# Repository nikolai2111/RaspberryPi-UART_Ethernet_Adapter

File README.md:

<!-- Improved compatibility of back to top link: See: https://github.com/othneildrew/Best-README-Template/pull/73 -->

<!--
*** Thanks for checking out the Best-README-Template. If you have a suggestion
*** that would make this better, please fork the repo and create a pull request
*** or simply open an issue with the tag "enhancement".
*** Don't forget to give the project a star!
*** Thanks again! Now go create something AMAZING! :D
-->

<!-- PROJECT SHIELDS -->
<!--
*** I'm using markdown "reference style" links for readability.
*** Reference links are enclosed in brackets [ ] instead of parentheses ( ).
*** See the bottom of this document for the declaration of the reference variables
*** for contributors-url, forks-url, etc. This is an optional, concise syntax you may use.
*** https://www.markdownguide.org/basic-syntax/#reference-style-links
-->
[![Contributors][contributors-shield]][contributors-url]
[![Forks][forks-shield]][forks-url]
[![Stargazers][stars-shield]][stars-url]
[![Issues][issues-shield]][issues-url]
[![MIT License][license-shield]][license-url]

<!-- PROJECT LOGO -->
<br />
<div align="center">

<h3 align="center">Raspberry Pi UART to Ethernet Adapter</h3>

  <p align="center">
    This adapter board enables the creation of a stand-alone, network-compatible device using any Raspberry Pi compatible UART daughterboard.
    <br />
    <a href="https://github.com/nikolai2111/RaspberryPi-UART_Ethernet_Adapter"><strong>Explore the docs »</strong></a>
    <br />
    <br />
    <a href="https://github.com/nikolai2111/RaspberryPi-UART_Ethernet_Adapter">View Demo</a>
    ·
    <a href="https://github.com/nikolai2111/RaspberryPi-UART_Ethernet_Adapter/issues/new?labels=bug&template=bug-report---.md">Report Bug</a>
    ·
    <a href="https://github.com/nikolai2111/RaspberryPi-UART_Ethernet_Adapter/issues/new?labels=enhancement&template=feature-request---.md">Request Feature</a>
  </p>
</div>

<!-- TABLE OF CONTENTS -->
<details>
  <summary>Table of Contents</summary>
  <ol>
    <li>
      <a href="#about-the-project">About The Project</a>
      <ul>
        <li><a href="#built-with">Built With</a></li>
      </ul>
    </li>
    <li>
      <a href="#getting-started">Getting Started</a>
      <ul>
        <li><a href="#prerequisites">Prerequisites</a></li>
        <li><a href="#Configure WIZ750SR">Configure WIZ750SR</a></li>
        <li><a href="#Confgure Z-Wave JS UI">Confgure Z-Wave JS UI</a></li>
      </ul>
    </li>
    <li><a href="#usage">Usage</a></li>
    <li><a href="#roadmap">Roadmap</a></li>
    <li><a href="#contributing">Contributing</a></li>
    <li><a href="#license">License</a></li>
    <li><a href="#contact">Contact</a></li>
    <li><a href="#acknowledgments">Acknowledgments</a></li>
  </ol>
</details>

<!-- ABOUT THE PROJECT -->
## About The Project

This adapter board enables the creation of a stand-alone, network-compatible device using any Raspberry Pi compatible UART daughterboard. The adapter board is used to connect the daughterboard of the Raspberry Pi and [WIZ750SR](https://docs.wiznet.io/Product/S2E-Module/WIZ750SR)-TTL. The adapter board connects the daughterboard of the Raspberry Pi to the [WIZ750SR](https://docs.wiznet.io/Product/S2E-Module/WIZ750SR)-TTL. It also provides a 5V and 3.3V power supply where necessary.

The adapter board was initially designed to connect the [RaZberry 7 Pro](https://z-wave.me/products/razberry/#slide-1) to [Home Assistant](https://www.home-assistant.io/) via TCP, without using a Raspberry Pi as a server. It can also be used with any Raspberry Pi daughterboard that only needs the TTL-UART interface. However, the following README refers to the use of the [RaZberry 7 Pro](https://z-wave.me/products/razberry/#slide-1) with [Home Assistant](https://www.home-assistant.io/). It is possible to map three GPIOs to the header, although this has not been tested yet.

The board or as a kit (incl. [WIZ750SR](https://www.digikey.de/de/products/detail/wiznet/WIZ750SR-TTL/8789618)) can be purchased [here](https://www.tindie.com/products/nikolai2111/raspberry-pi-uart-to-ethernet-adapter/). The board is available with three power supply options (power supply not inlcuded):
* [Barrel Jack 2.1x5.5 mm](https://www.digikey.com/en/products/detail/cui-devices/PJ-037A/1644545)
* [USB Micro](https://www.digikey.de/de/products/detail/amphenol-cs-fci/10118194-0001LF/2785389)
* [USB C](https://www.digikey.ch/de/products/detail/gct/USB4125-GF-A/13547388)

<p align="right">(<a href="#readme-top">back to top</a>)</p>

### Built With

* [][Kicad-url]

<p align="right">(<a href="#readme-top">back to top</a>)</p>

<!-- GETTING STARTED -->
## Getting Started

### Prerequisites
* [Home Assistant](https://www.home-assistant.io/) is running
* [Z-Wave JS UI](https://www.home-assistant.io/integrations/zwave_js/) installed
* [WIZnet-S2E-Tool-GUI](https://github.com/Wiznet/WIZnet-S2E-Tool-GUI) downloaded

### Configure WIZ750SR
1. Open the [WIZnet-S2E-Tool-GUI](https://github.com/Wiznet/WIZnet-S2E-Tool-GUI)
2. Click `Device Search`
3. Select device with double click
4. Set the `Basic Settings` as shown in the picture below

### Confgure Z-Wave JS UI
1. Open [Home Assistant](homeassistant.local)
2. Open `Add-ons`
3. Click on `Z-Wave JS UI`
4. Start the add-on, if it's not running yet
5. Click on `OPEN WEB UI`
6. Go to `Settings`
7. Go to `Z-Wave`
8. And enter the IP and port below the `Serial Port` as shown in the picture blow. Use the scheme `tcp://your-ip:port`

<!-- USAGE EXAMPLES -->
## Usage

Use this space to show useful examples of how a project can be used. Additional screenshots, code examples and demos work well in this space. You may also link to more resources.

_For more examples, please refer to the [Documentation](https://example.com)_

<p align="right">(<a href="#readme-top">back to top</a>)</p>

<!-- ROADMAP -->
## Roadmap

* [ ] Test more than one device
* [ ] Offer [WIZ750SR](https://docs.wiznet.io/Product/S2E-Module/WIZ750SR) in the shop
* [ ] Offer PoE adapter in the shop

See the [open issues](https://github.com/nikolai2111/RaspberryPi-UART_Ethernet_Adapter/issues) for a full list of proposed features (and known issues).

<p align="right">(<a href="#readme-top">back to top</a>)</p>

<!-- CONTRIBUTING -->
## Contributing

Contributions are what make the open source community such an amazing place to learn, inspire, and create. Any contributions you make are **greatly appreciated**.

If you have a suggestion that would make this better, please fork the repo and create a pull request. You can also simply open an issue with the tag "enhancement".
Don't forget to give the project a star! Thanks again!

1. Fork the Project
2. Create your Feature Branch (`git checkout -b feature/AmazingFeature`)
3. Commit your Changes (`git commit -m 'Add some AmazingFeature'`)
4. Push to the Branch (`git push origin feature/AmazingFeature`)
5. Open a Pull Request

<p align="right">(<a href="#readme-top">back to top</a>)</p>

<!-- LICENSE -->
## License

Distributed under the [CERN-OHL-P](LICENSE) License. See `LICENSE` for more information. The license for all other sources remains the same and is still valid.

<p align="right">(<a href="#readme-top">back to top</a>)</p>

<!-- CONTACT -->
## Contact

Nikolai Zoller - [nikolai.zoller@hotmail.com](mailto:nikolai.zoller@hotmail.com)

Project Link: [https://github.com/nikolai2111/RaspberryPi-UART_Ethernet_Adapter](https://github.com/nikolai2111/RaspberryPi-UART_Ethernet_Adapter)

<p align="right">(<a href="#readme-top">back to top</a>)</p>

<!-- ACKNOWLEDGMENTS -->
## Acknowledgments

The main concept was initially proposed by an anonymous colleague. The development, production, and sale are carried out with their consent.

<p align="right">(<a href="#readme-top">back to top</a>)</p>

Source: [Best-README-Template](https://github.com/othneildrew/Best-README-Template)

<!-- MARKDOWN LINKS & IMAGES -->
<!-- https://www.markdownguide.org/basic-syntax/#reference-style-links -->
[contributors-shield]: https://img.shields.io/github/contributors/nikolai2111/RaspberryPi-UART_Ethernet_Adapter.svg?style=for-the-badge
[contributors-url]: https://github.com/nikolai2111/RaspberryPi-UART_Ethernet_Adapter/graphs/contributors
[forks-shield]: https://img.shields.io/github/forks/nikolai2111/RaspberryPi-UART_Ethernet_Adapter.svg?style=for-the-badge
[forks-url]: https://github.com/nikolai2111/RaspberryPi-UART_Ethernet_Adapter/network/members
[stars-shield]: https://img.shields.io/github/stars/nikolai2111/RaspberryPi-UART_Ethernet_Adapter.svg?style=for-the-badge
[stars-url]: https://github.com/nikolai2111/RaspberryPi-UART_Ethernet_Adapter/stargazers
[issues-shield]: https://img.shields.io/github/issues/nikolai2111/RaspberryPi-UART_Ethernet_Adapter.svg?style=for-the-badge
[issues-url]: https://github.com/nikolai2111/RaspberryPi-UART_Ethernet_Adapter/issues
[license-shield]: https://img.shields.io/github/license/nikolai2111/RaspberryPi-UART_Ethernet_Adapter.svg?style=for-the-badge
[license-url]: https://github.com/nikolai2111/RaspberryPi-UART_Ethernet_Adapter/blob/master/LICENSE.txt
[Kicad-logo]: https://upload.wikimedia.org/wikipedia/commons/5/59/KiCad-Logo.svg
[Kicad-url]: https://www.kicad.org/

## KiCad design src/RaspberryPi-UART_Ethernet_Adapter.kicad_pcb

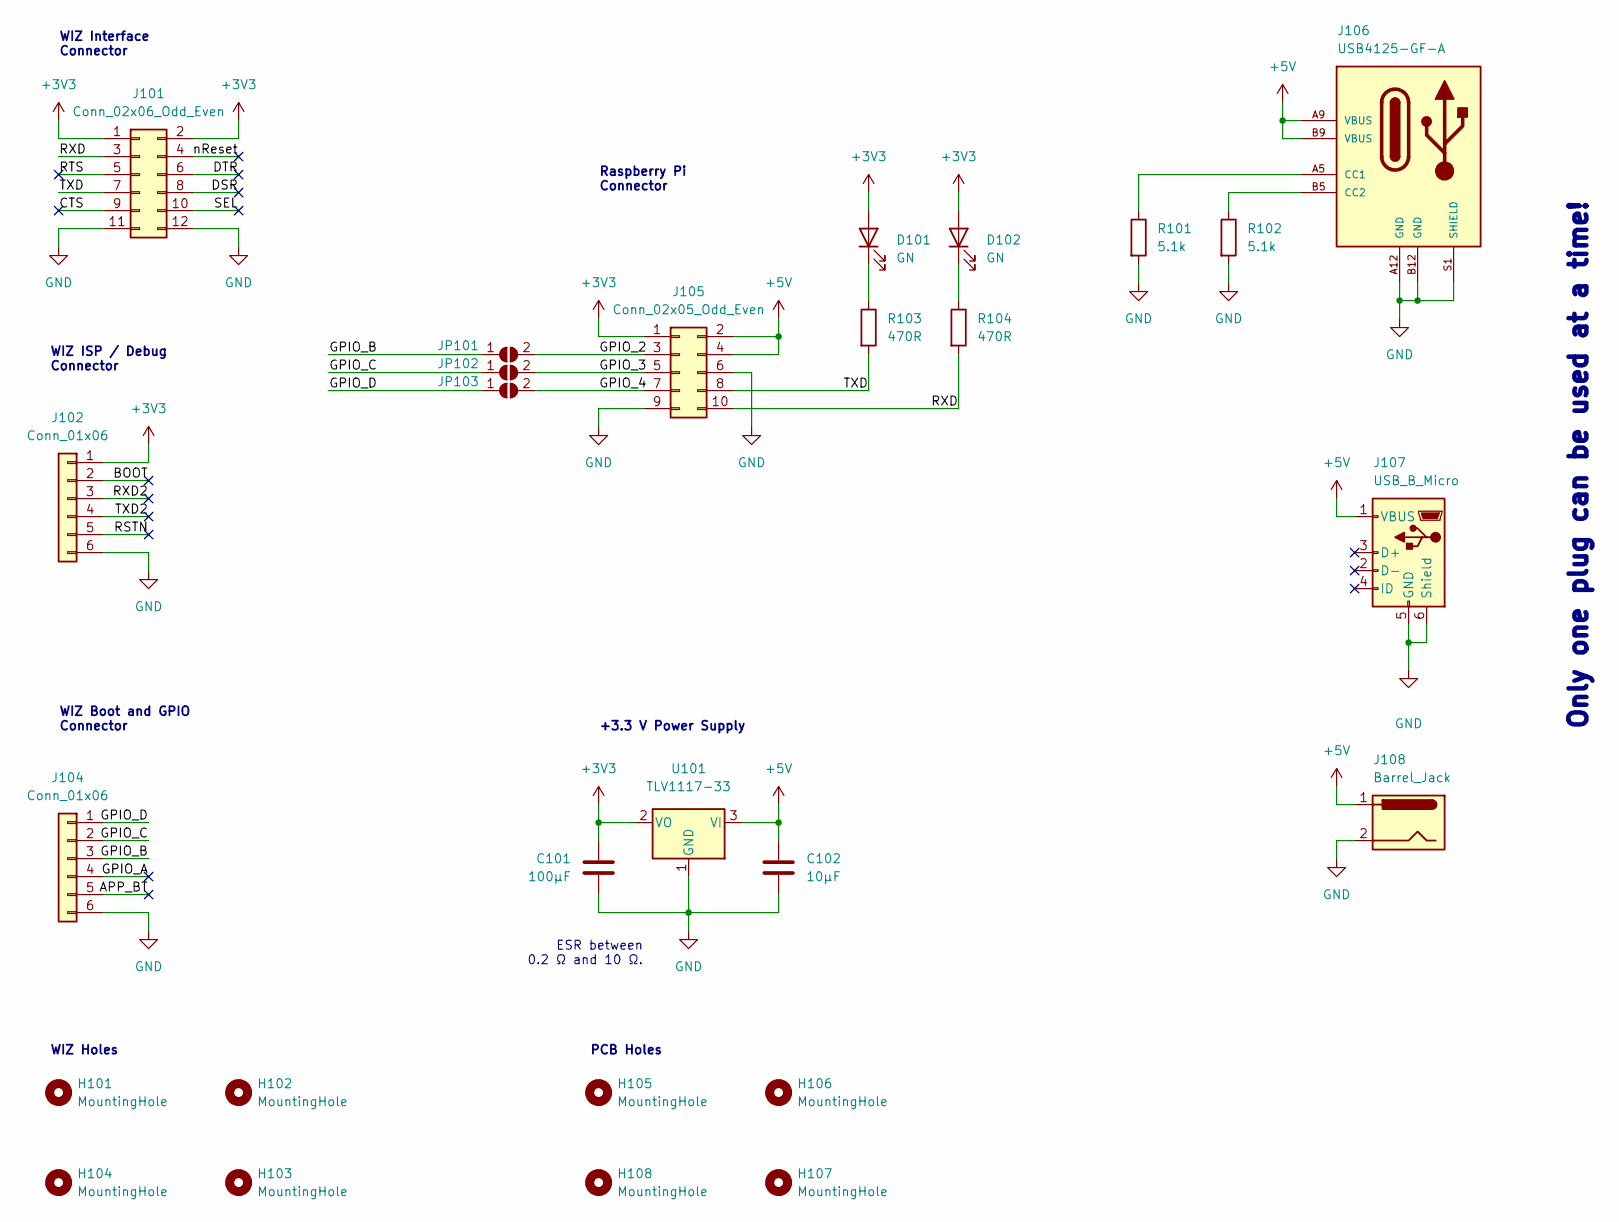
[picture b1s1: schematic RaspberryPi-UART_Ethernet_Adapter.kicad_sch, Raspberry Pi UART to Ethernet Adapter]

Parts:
C101: 100µF; C_0805_2012Metric_Pad1.18x1.45mm_HandSolder; Manufacturer Part No. CL21A107MQYNNWE
C102: 10µF; C_0805_2012Metric_Pad1.18x1.45mm_HandSolder; Manufacturer Part No. CL21A106KOQNNNE
D101, D102: GN; LED_0805_2012Metric_Pad1.15x1.40mm_HandSolder; Manufacturer Part No. LTST-C171GKT
H101, H102, H103, H104: MountingHole; MountingHole_2.7mm_M2.5_DIN965
H105, H106, H107, H108: MountingHole; MountingHole_3.2mm_M3_DIN965
J101: Conn_02x06_Odd_Even; PinSocket_2x06_P2.54mm_Vertical; Manufacturer Part No. RS2-12-G
J102, J104: Conn_01x06; PinSocket_1x06_P2.54mm_Vertical; Manufacturer Part No. RS1-06-G
J105: Conn_02x05_Odd_Even; PinHeader_2x05_P2.54mm_Vertical; Manufacturer Part No. PH2-10-UA
J106: USB4125-GF-A; GCT_USB4125-GF-A; Manufacturer Part No. USB4125-GF-A
J107: USB_B_Micro; USB_Micro-B_Amphenol_10118194_Horizontal; Manufacturer Part No. 10118194-0001LF
J108: Barrel_Jack; CUI_PJ-037A_Board-Edge; Manufacturer Part No. PJ-037A
JP101, JP102, JP103: SolderJumper_2_Open; SolderJumper-2_P1.3mm_Open_TrianglePad1.0x1.5mm
R101, R102: 5.1k; R_0805_2012Metric_Pad1.20x1.40mm_HandSolder; Manufacturer Part No. RC0805FR-075K1L
R103, R104: 470R; R_0805_2012Metric_Pad1.20x1.40mm_HandSolder; Manufacturer Part No. RC0805FR-07470RL
U101: TLV1117-33; SOT-223-3_TabPin2; Manufacturer Part No. TLV1117-33CDCYR

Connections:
+3V3: C101.1, D101.2 (A), D102.2 (A), J101.1, J101.2, J102.1, J105.1, U101.2 (VO)
+5V: C102.1, J105.2, J105.4, J106.A9 (VBUS), J106.B9 (VBUS), J107.1 (VBUS), J108.1, U101.3 (VI)
/APP_BT: J104.5
/BOOT: J102.2
/CTS: J101.9
/DSR: J101.8
/DTR: J101.6
/GPIO_2: J105.3, JP101.2 (B)
/GPIO_3: J105.5, JP102.2 (B)
/GPIO_4: J105.7, JP103.2 (B)
/GPIO_A: J104.4
/GPIO_B: J104.3, JP101.1 (A)
/GPIO_C: J104.2, JP102.1 (A)
/GPIO_D: J104.1, JP103.1 (A)
/RSTN: J102.5
/RTS: J101.5
/RXD: J101.3, J105.10, R104.2
/RXD2: J102.3
/SEL: J101.10
/TXD: J101.7, J105.8, R103.2
/TXD2: J102.4
/nReset: J101.4
GND: C101.2, C102.2, J101.11, J101.12, J102.6, J104.6, J105.6, J105.9, J106.A12 (GND), J106.B12 (GND), J106.S1 (SHIELD), J107.5 (GND), J107.6 (Shield), J108.2, R101.2, R102.2, U101.1 (GND)
unnamed: D101.1 (K), R103.1
unnamed: D102.1 (K), R104.1
unnamed: J106.A5 (CC1), R101.1
unnamed: J106.B5 (CC2), R102.1

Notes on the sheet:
+3.3 V Power Supply
WIZ Boot and GPIO Connector
ESR between 0.2 Ω and 10 Ω.
Only one plug can be used at a time!
WIZ ISP / Debug Connector
Raspberry Pi Connector
WIZ Holes
PCB Holes
WIZ Interface Connector

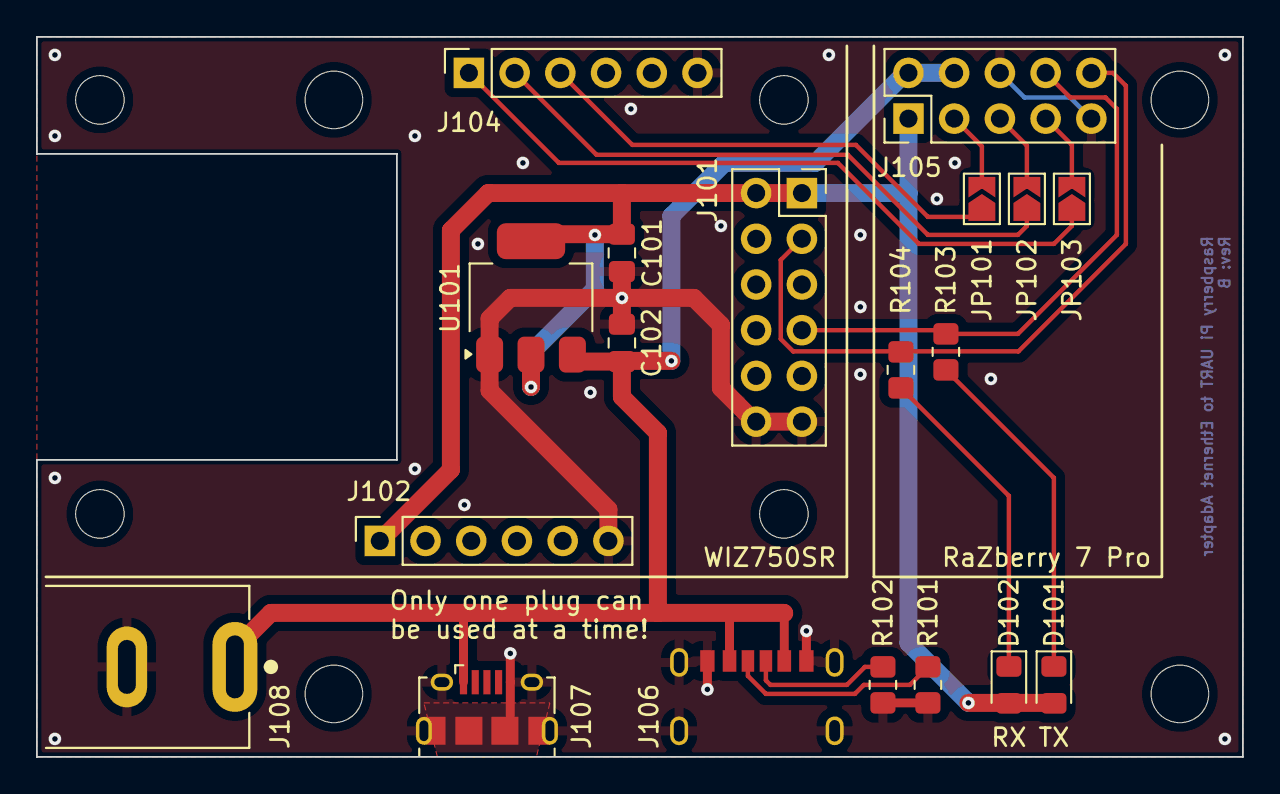
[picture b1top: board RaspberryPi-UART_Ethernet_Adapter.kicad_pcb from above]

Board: 2 copper layers, 67.0 x 40.0 mm, 27 parts (0 on the bottom side), 15 nets.

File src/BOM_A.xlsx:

Reference | Value | Datasheet | Footprint | Qty | DNP | Manufacturer Part No. | Vendor | Vendor Part No.
C101 | 100µF | ~ | Capacitor_SMD:C_0805_2012Metric_Pad1.18x1.45mm_HandSolder | 1 |  | CL21A107MQYNNWE | Digikey | 1276-CL21A107MQYNNWECT-ND
C102 | 10µF | ~ | Capacitor_SMD:C_0805_2012Metric_Pad1.18x1.45mm_HandSolder | 1 |  | CL21A106KOQNNNE | Digikey | 1276-1096-1-ND
D101,D102 | GN | ~ | LED_SMD:LED_0805_2012Metric_Pad1.15x1.40mm_HandSolder | 2 |  | LTST-C171GKT | Digikey | 160-1423-1-ND
H101,H102,H103,H104 | MountingHole | ~ | MountingHole:MountingHole_2.7mm_M2.5_DIN965 | 4
H105,H106,H107,H108 | MountingHole | ~ | MountingHole:MountingHole_3.2mm_M3_DIN965 | 4
J101 | Conn_02x06_Odd_Even | ~ | Connector_PinSocket_2.54mm:PinSocket_2x06_P2.54mm_Vertical | 1 |  | RS2-12-G | Digikey | 2057-RS2-12-G-ND
J102,J104 | Conn_01x06 | ~ | Connector_PinSocket_2.54mm:PinSocket_1x06_P2.54mm_Vertical | 2 |  | RS1-06-G | Digikey | 2057-RS1-06-G-ND
J105 | Conn_02x05_Odd_Even | ~ | Connector_PinHeader_2.54mm:PinHeader_2x05_P2.54mm_Vertical | 1 |  | RS2-10-G | Digikey | 2057-RS2-10-G-ND
J106 | USB4125-GF-A |  | Connectors_User:GCT_USB4125-GF-A | 1 |  | USB4125-GF-A | Digikey | 2073-USB4125-GF-ACT-ND
J107 | USB_B_Micro | ~ | Connector_USB:USB_Micro-B_Amphenol_10118194_Horizontal | 1 |  | 10118194-0001LF | Digikey | 609-4618-1-ND
J108 | Barrel_Jack | ~ | Connector_User:CUI_PJ-037A_Board-Edge | 1 |  | PJ-037A | Digikey | CP-037A-ND
JP101,JP102,JP103 | SolderJumper_2_Open | ~ | Jumper:SolderJumper-2_P1.3mm_Open_TrianglePad1.0x1.5mm | 3 |  | - | - | -
R101,R102 | 5.1k | ~ | Resistor_SMD:R_0805_2012Metric_Pad1.20x1.40mm_HandSolder | 2 |  | RC0805FR-075K1L | Digikey | 311-5.10KCRCT-ND
R103,R104 | 470R | ~ | Resistor_SMD:R_0805_2012Metric_Pad1.20x1.40mm_HandSolder | 2 |  | RC0805FR-07470RL | Digikey | 311-470CRCT-ND
U101 | TLV1117-33 | http://www.ti.com/lit/ds/symlink/tlv1117.pdf | Package_TO_SOT_SMD:SOT-223-3_TabPin2 | 1 |  | TLV1117-33CDCYR | Digikey | 296-21112-1-ND

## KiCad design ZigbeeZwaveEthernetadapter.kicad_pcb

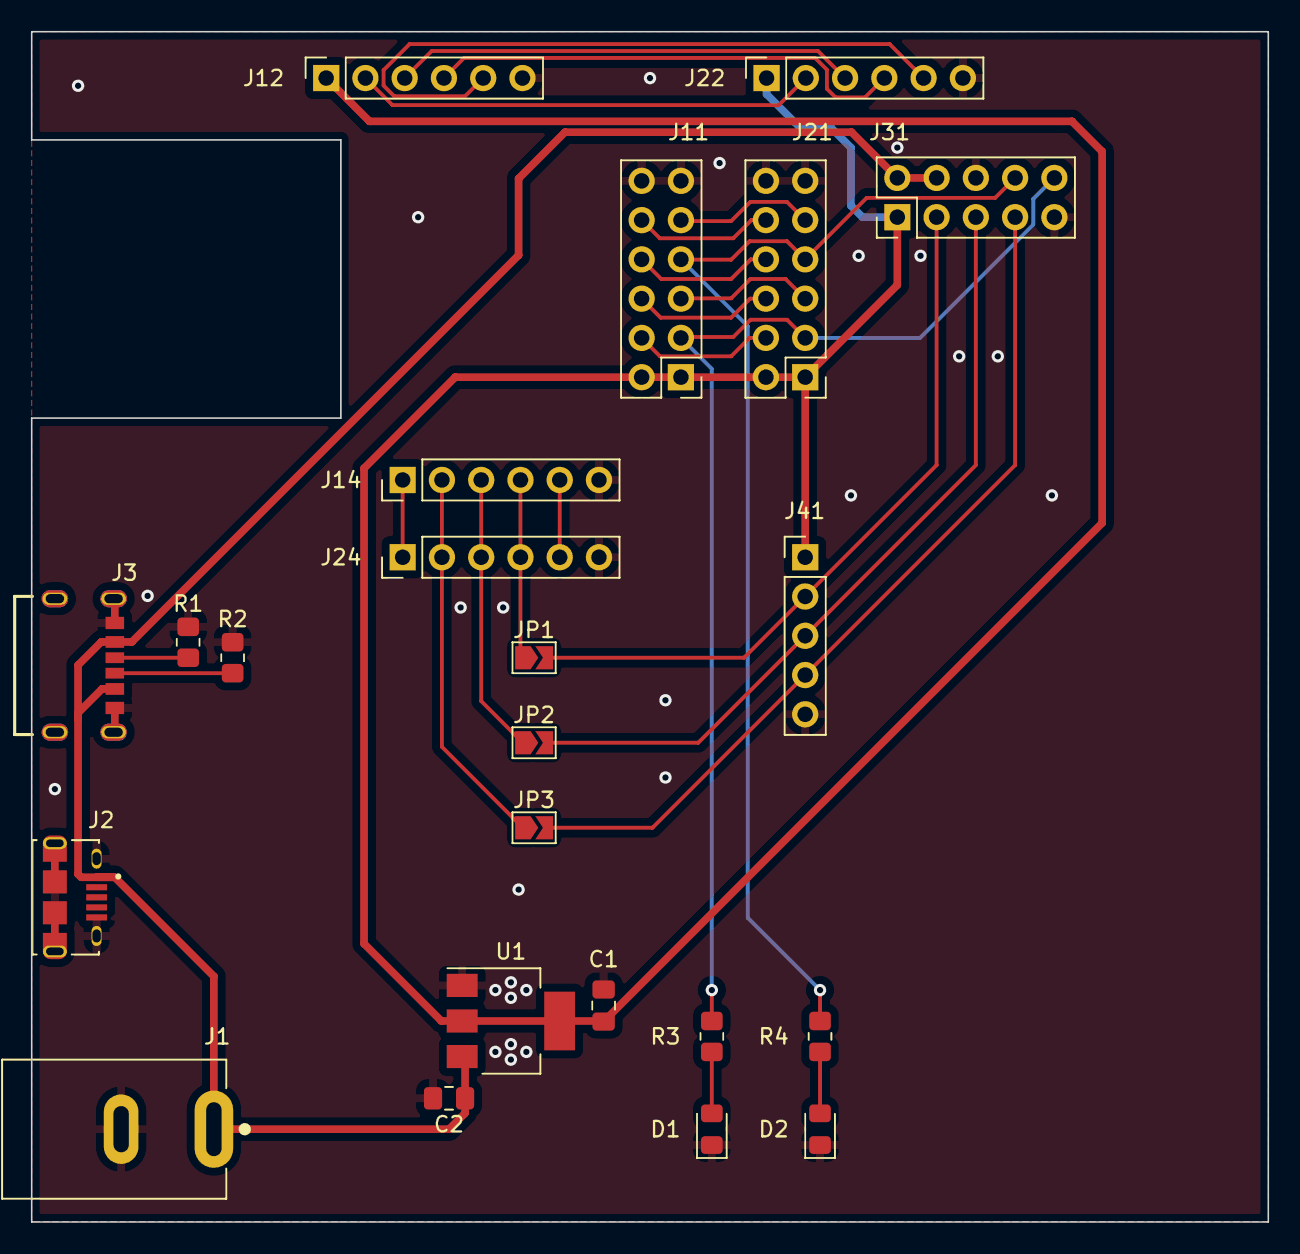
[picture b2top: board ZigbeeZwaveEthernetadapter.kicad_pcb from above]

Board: 2 copper layers, 80.0 x 77.0 mm, 23 parts (0 on the bottom side), 27 nets.

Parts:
C1: 47µ; C_0805_2012Metric_Pad1.18x1.45mm_HandSolder
C2: 0.47µ; C_0805_2012Metric_Pad1.18x1.45mm_HandSolder
D1, D2: LED; LED_0805_2012Metric_Pad1.15x1.40mm_HandSolder
J1: Barrel_Jack; CUI_PJ-037A
J2: USB_B_Micro; AMPHENOL_10118194-0001LF
J3: USB4125-GF-A; GCT_USB4125-GF-A
J11: Conn_02x06_Odd_Even; PinSocket_2x06_P2.54mm_Vertical
J12, J14: Conn_01x06; PinSocket_1x06_P2.54mm_Vertical
J21: Conn_02x06_Odd_Even; PinHeader_2x06_P2.54mm_Vertical
J22, J24: Conn_01x06; PinHeader_1x06_P2.54mm_Vertical
J31: Conn_02x05_Odd_Even; PinHeader_2x05_P2.54mm_Vertical
J41: Conn_01x05; PinHeader_1x05_P2.54mm_Vertical
JP1, JP2, JP3: SolderJumper_2_Open; SolderJumper-2_P1.3mm_Open_TrianglePad1.0x1.5mm
R1, R2: 5.1k; R_0805_2012Metric_Pad1.20x1.40mm_HandSolder
R3, R4: 100R; R_0805_2012Metric_Pad1.20x1.40mm_HandSolder
U1: TLV1117-33; SOT-223-3_TabPin2

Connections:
+3V3: C1.1, J11.1, J11.2, J12.1, J21.1, J21.2, J22.1, J31.1, J41.1, U1.2 (VO)
+5V: C2.1, J1.1, J2.1 (VBUS), J3.A9 (VBUS), J3.B9 (VBUS), J31.2, J31.4, U1.3 (VI)
/APP_BOOT: J14.5, J24.5
/BOOT: J12.2, J22.2
/CTS: J11.9, J21.9
/DSR: J11.8, J21.8
/DTR: J11.6, J21.6
/GPIO_2_SDA: J31.3, J41.2, JP1.2 (B)
/GPIO_3_SCL: J31.5, J41.3, JP2.2 (B)
/GPIO_4_GPCLK0: J31.7, J41.4, JP3.2 (B)
/GPIO_A: J14.4, J24.4, JP1.1 (A)
/GPIO_B: J14.3, J24.3, JP2.1 (A)
/GPIO_C: J14.2, J24.2, JP3.1 (A)
/GPIO_D: J14.1, J24.1
/N.C.: J11.10, J21.10
/RSTN: J12.5, J22.5
/RTS: J11.5, J21.5
/RXD: J11.3, J21.3, J31.10, R3.1
/RXD2: J12.3, J22.3
/TXD: J11.7, J21.7, J31.8, R4.1
/TXD2: J12.4, J22.4
/nReset: J11.4, J21.4
GND: C1.2, C2.2, D1.1 (K), D2.1 (K), J1.2, J2.5 (GND), J2.6 (Shield), J3.A12 (GND), J3.B12 (GND), J3.S1 (SHIELD), J11.11, J11.12, J12.6, J14.6, J21.11, J21.12, J22.6, J24.6, J31.6, J31.9, J41.5, R1.2, R2.2, U1.1 (GND)
unnamed: D1.2 (A), R3.2
unnamed: D2.2 (A), R4.2
unnamed: J3.A5 (CC1), R1.1
unnamed: J3.B5 (CC2), R2.1

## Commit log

2022-12-31 Add: KiCad Project
2022-12-31 Add: the "_build" folder to the gitignore
2022-12-31 Mod: gitignore
2023-01-15 Add: Infos and data for the WIZ750SR
2023-01-15 Add: Infos and data for the Razberry
2023-01-15 Add: Basic schematic with voltage regulator, WIZ750SR, RasPi and power connectors
2023-01-15 Mod: README from Razberry, corrected text
2023-01-15 Mod: Finished schematic, changed linear regulator and added second pinout
2023-01-15 Add: Schematic as a pdf
2023-01-16 Mod: LDO (U1) from LM2940 to LM3940
2023-01-16 Add: Data for USB Type-C connector such as data sheets, drawings and 3D model
2023-01-16 Add: USB4125-GF-A to the project symbol and footprint library
2023-01-16 Add: A file which got forgotten from the footprint library
2023-01-16 Mod: Symbol from USB Type-C receptacle and assigned footprint
2023-01-16 Add: 3D model to the footprint library
2023-01-16 Mod: Exported new schematics
2023-01-16 Mod: Assigned the footprints of the pin header and sockets
2023-01-16 Mod: Assigned more footprints to the capacitors and resistors
2023-01-16 Add: Data for DC-Jack with 3D model
2023-01-16 Mod: Moved models to the corresponding libraries
2023-01-16 Mod: Assigned footprint for LDO, Micro USB and Barrel-Jack
2023-01-16 Add: Exported schematic
2023-01-17 Mod: Changed footprint of U1
2023-01-17 Mod: Picture of GPIO and APP Boot pinout, wrong version
2023-01-17 Add: Solder bridges and RX and TX LEDs
2023-02-01 Mod: Footprint of the GCT_USB4125-GF-A, moved it to the global library.
2023-02-02 Add: PCB Layout to the project, almost finished
2023-03-06 Mod: Schematic, moved footprint to global library own
2023-04-25 Mod: Migrated to KiCAD 7.0
2024-01-26 Mod: Updated project and adapted template.
2024-01-26 Add: BOM_A.pdf
2024-01-26 Mod: Schematic and PCB-Layout, finished new Version.
2024-01-26 Add: Gerber files
2024-01-27 Mod: ZigbeeZwaveEthernetadapter.kicad_pcb, removed DRC errors and warnings.
2024-01-27 Mod: DRC exclusion
2024-02-06 Mod: LEDs for RXD and TXD, changed from Pull-Down to Pull-Up resistors and changed their value. Re-exported all the files.
2024-02-06 Mod: Re-exported the pictures.
2024-02-06 Mod: Re-exported gerbers and renamed the .zip
2024-02-06 Mod: Renamed gerbers
2024-03-03 Mod: Updated project to KiCad 8.0
2024-03-03 Mod: ZigbeeZwaveEthernetadapter.kicad_sch, changes part no. of C101
2024-03-15 Mod: Renamed project form ZigbeeZwaveEthernetadapter to RaspberryPi-UART_Ethernet_Adapter
2024-03-15 Mod: Manufacturer no. & Vendor no. of J105. Changed from socket header to pin header. Close #3
2024-03-15 Mod: Footprint J106, added front paste layer, closes #1. Moved logo G1 in the middle of the plane, closes #4.
2024-03-15 Add: README.md with pictures
2024-03-15 Add: Anchor to top to README.md
2024-04-27 Mod: Updated README.md and changed to LICENSE.txt
2024-04-27 Mod: README.md, removed linkedIn badge.
2024-04-27 Mod: README.md, removed empty logo.
2024-04-27 Mod: Updated table of content.
2024-04-28 Mod: README.md, added some links
2024-04-28 Mod: README.md, modified digikey links

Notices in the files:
ZigbeeZwaveEthernetadapter.kicad_pcb:
Licence: CC BY-NC 4.0
https://creativecommons.org/licenses/by-nc/4.0
